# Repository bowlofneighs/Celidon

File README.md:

# Celidon

Celidon is a split orthilinear column staggered ergo keyboard designed with ergogen. I started making it because 1. ergo keyboards look really cool, 2. my current/old keyboard (razer cynosa v2) is terrible. It has no customizability on linux, membrane switches, bad ergonomics, and its loud and clicky. So I started working on a new keyboard using ergogen, a web tool designed for creating ergonomic keyboards. This project is my first foray into git, github, `yaml` KiCAD, hardware design, soldering, pcbs, and more that I can't think of right now.

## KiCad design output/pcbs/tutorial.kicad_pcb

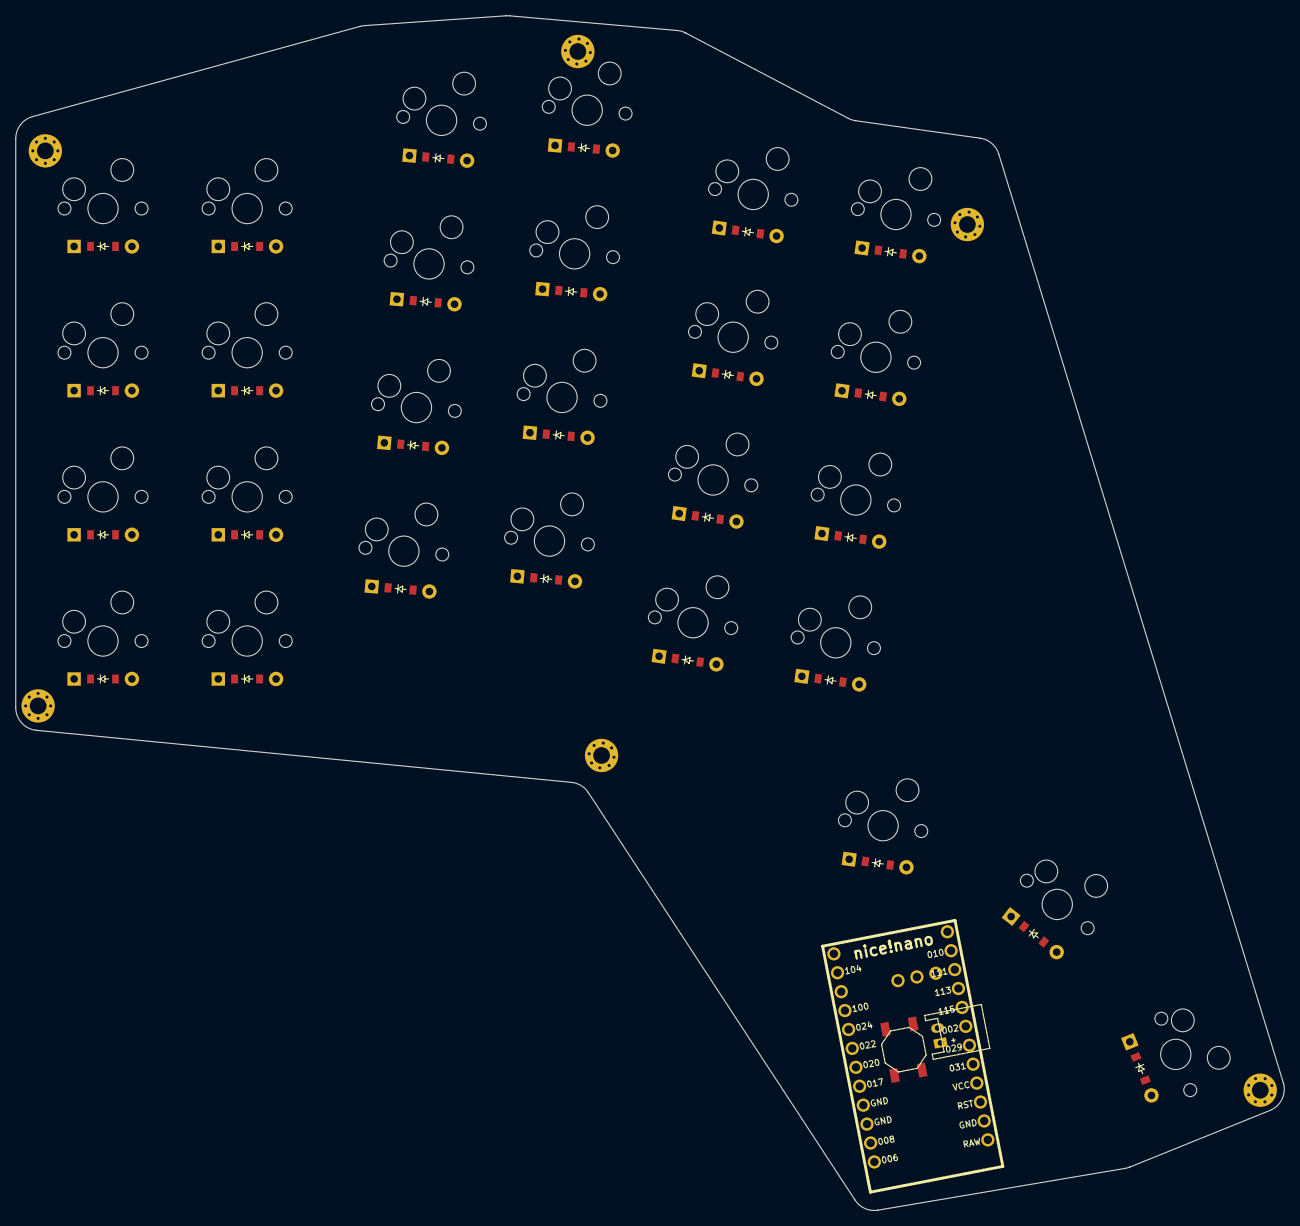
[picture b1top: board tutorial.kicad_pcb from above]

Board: 2 copper layers, 167.2 x 157.4 mm, 63 parts (0 on the bottom side), 44 nets, no tracks yet.

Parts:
B1: SW_TACT_ALPS_SKQGABE010
D1, D2, D3, D4, D5, D6, D7, D8, D9, D10, D11, D12, D13, D14, D15, D16, D17, D18, D19, D20, D21, D22, D23, D24, D25, D26, D27: ComboDiode
JST1: JST_PH_S2B-PH-K_02x2.00mm_Angled
MCU1: nice_nano
S1, S2, S3, S4, S5, S6, S7, S8, S9, S10, S11, S12, S13, S14, S15, S16, S17, S18, S19, S20, S21, S22, S23, S24, S25, S26, S27: MX
_1, _2, _3, _4, _5, _6: MountingHole_2.2mm_M2_Pad_Via

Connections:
GND: B1.1, JST1.2, MCU1.3, MCU1.4, MCU1.23
P006: MCU1.1, S1.1, S2.1, S3.1, S4.1
P008: MCU1.2, S5.1, S6.1, S7.1, S8.1
P009: MCU1.13, S25.1
P010: D4.1, D8.1, D12.1, D16.1, D20.1, D24.1, MCU1.14
P017: MCU1.5, S9.1, S10.1, S11.1, S12.1
P020: MCU1.6, S13.1, S14.1, S15.1, S16.1
P022: MCU1.7, S17.1, S18.1, S19.1, S20.1
P024: MCU1.8, S21.1, S22.1, S23.1, S24.1
P031: MCU1.20, S27.1
P101: D3.1, D7.1, D11.1, D15.1, D19.1, D23.1, MCU1.31
P102: D2.1, D6.1, D10.1, D14.1, D18.1, D22.1, MCU1.32
P107: D1.1, D5.1, D9.1, D13.1, D17.1, D21.1, MCU1.33
P113: MCU1.16, S26.1
P115: D25.1, D26.1, D27.1, MCU1.17
RAW: JST1.1, MCU1.24
RST: B1.2, MCU1.22
far_thumb: D27.2, S27.2
home_thumb: D26.2, S26.2
index_bottom: D17.2, S17.2
index_home: D18.2, S18.2
index_num: D20.2, S20.2
index_top: D19.2, S19.2
inner_bottom: D21.2, S21.2
inner_home: D22.2, S22.2
inner_num: D24.2, S24.2
inner_top: D23.2, S23.2
middle_bottom: D13.2, S13.2
middle_home: D14.2, S14.2
middle_num: D16.2, S16.2
middle_top: D15.2, S15.2
near_thumb: D25.2, S25.2
outer_bottom: D1.2, S1.2
outer_home: D2.2, S2.2
outer_num: D4.2, S4.2
outer_top: D3.2, S3.2
pinky_bottom: D5.2, S5.2
pinky_home: D6.2, S6.2
pinky_num: D8.2, S8.2
pinky_top: D7.2, S7.2
ring_bottom: D9.2, S9.2
ring_home: D10.2, S10.2
ring_num: D12.2, S12.2
ring_top: D11.2, S11.2

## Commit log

2025-06-17 attempt 2, here we go
